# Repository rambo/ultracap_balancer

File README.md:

Series ultracap balancer
========================

Circuits to monitor and balance multiple ultracaps connected to a series.

## 6-Way balancer

[6way.sch](./6way.sch): for 6 Maxel 2600F 2.5V boostcaps in series, balanced
by discharging each cap through 1Ohm resistor as needed.

IMCOMPLETE DESIGN, DO NOT USE.

## FAN7385 & DMG9926 breakout

[fan7385_breakout.sch](./fan7385_breakout.sch): Breaks out both chips to 100mil 
pin headers, the parts can be separated by cutting the board, has the likely connections
either pre-made or available via solder jumpers.

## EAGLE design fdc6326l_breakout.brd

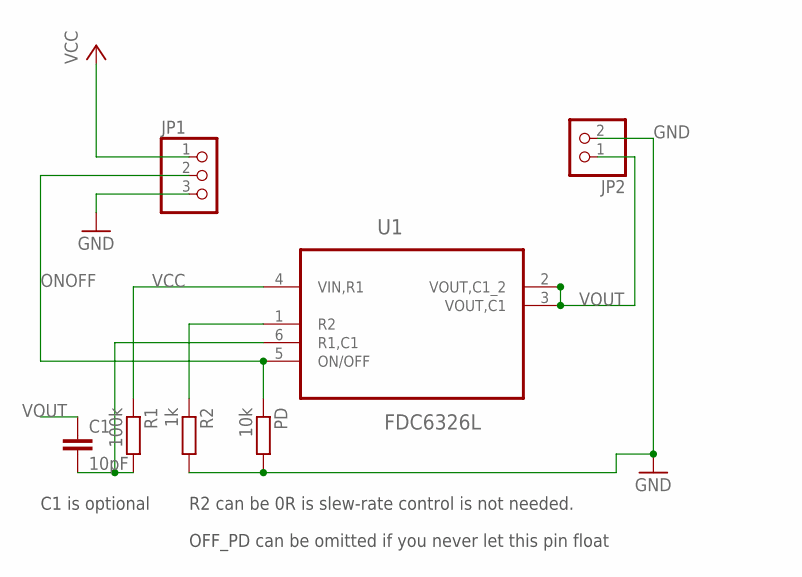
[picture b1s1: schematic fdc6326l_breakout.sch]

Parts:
C1: 10pF; C0603
JP1: PINHD-1X3; 1X03
JP2: PINHD-1X2; 1X02
PD: 10k; R0603
R1: 100k; R0603
R2: 1k; R0603
U1: FDC6326L; SOT95P280X110-6N

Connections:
C1_R1: C1.2, R1.2, U1.6 (R1,C1)
GND: JP1.3, JP2.2, PD.2, R2.2
ONOFF: JP1.2, PD.1, U1.5 (ON/OFF)
R2: R2.1, U1.1 (R2)
VCC: JP1.1, R1.1, U1.4 (VIN,R1)
VOUT: C1.1, JP2.1, U1.2 (VOUT,C1_2), U1.3 (VOUT,C1)

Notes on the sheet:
C1 is optional
R2 can be 0R is slew-rate control is not needed.
OFF_PD can be omitted if you never let this pin float

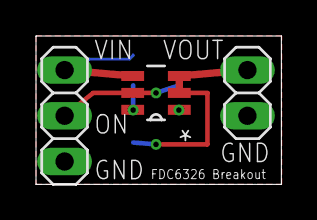
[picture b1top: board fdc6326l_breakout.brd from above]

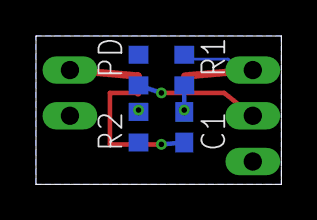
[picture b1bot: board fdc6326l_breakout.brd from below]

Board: 4 copper layers, 13.6 x 8.2 mm, 7 parts (4 on the bottom side), 6 nets.

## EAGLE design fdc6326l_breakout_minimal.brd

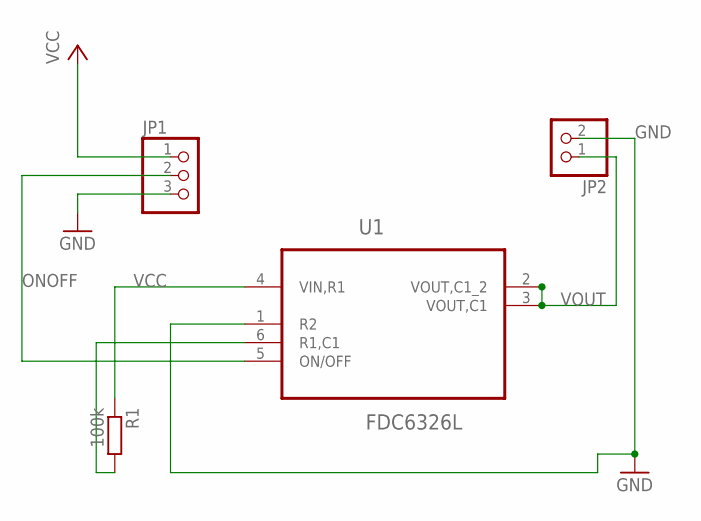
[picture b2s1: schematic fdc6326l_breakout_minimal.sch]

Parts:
JP1: PINHD-1X3; 1X03
JP2: PINHD-1X2; 1X02
R1: 100k; M0805
U1: FDC6326L; SOT95P280X110-6N

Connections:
GND: JP1.3, JP2.2, U1.1 (R2)
unnamed: R1.2, U1.6 (R1,C1)
ONOFF: JP1.2, U1.5 (ON/OFF)
VCC: JP1.1, R1.1, U1.4 (VIN,R1)
VOUT: JP2.1, U1.2 (VOUT,C1_2), U1.3 (VOUT,C1)

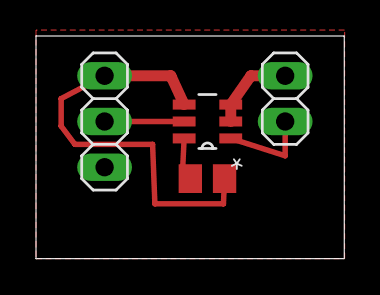
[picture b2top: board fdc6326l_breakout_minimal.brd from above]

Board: 1 copper layer, 17.1 x 12.4 mm, 4 parts (0 on the bottom side), 5 nets.

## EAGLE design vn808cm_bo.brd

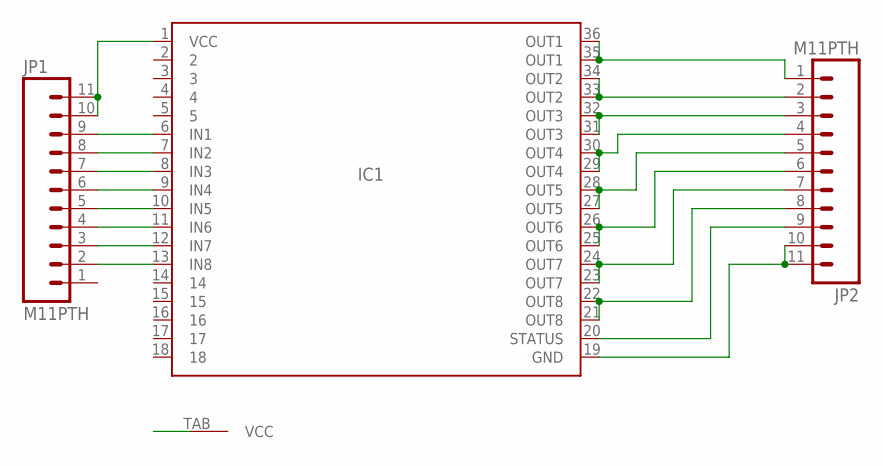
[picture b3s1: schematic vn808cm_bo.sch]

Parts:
IC1: VN808CM-E; POWERSO-36
JP1, JP2: M11PTH; 1X11

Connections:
GND: IC1.19 (GND), JP2.10, JP2.11
IN1: IC1.6 (IN1), JP1.9
IN2: IC1.7 (IN2), JP1.8
IN3: IC1.8 (IN3), JP1.7
IN4: IC1.9 (IN4), JP1.6
IN5: IC1.10 (IN5), JP1.5
IN6: IC1.11 (IN6), JP1.4
IN7: IC1.12 (IN7), JP1.3
IN8: IC1.13 (IN8), JP1.2
OUT1: IC1.35 (OUT1), IC1.36 (OUT1), JP2.1
OUT2: IC1.33 (OUT2), IC1.34 (OUT2), JP2.2
OUT3: IC1.31 (OUT3), IC1.32 (OUT3), JP2.3
OUT4: IC1.29 (OUT4), IC1.30 (OUT4), JP2.4
OUT5: IC1.27 (OUT5), IC1.28 (OUT5), JP2.5
OUT6: IC1.25 (OUT6), IC1.26 (OUT6), JP2.6
OUT7: IC1.23 (OUT7), IC1.24 (OUT7), JP2.7
OUT8: IC1.21 (OUT8), IC1.22 (OUT8), JP2.8
STATUS: IC1.20 (STATUS), JP2.9
VCC: IC1.1 (VCC), IC1.TAB (VCC), JP1.10, JP1.11

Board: 2 copper layers, 3 parts (0 on the bottom side), 19 nets, no tracks yet.

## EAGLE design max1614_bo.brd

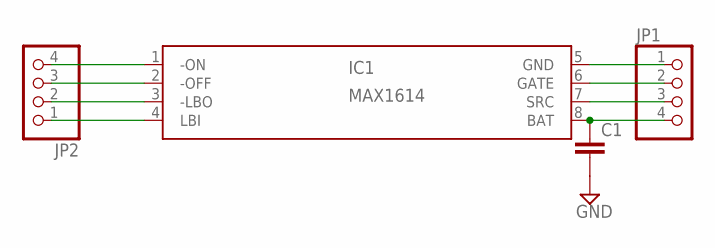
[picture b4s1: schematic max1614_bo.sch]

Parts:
C1: C-EUC0805; C0805
IC1: MAX1614; UMAX8
JP1, JP2: PINHD-1X4; 1X04

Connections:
-LBO: IC1.3 (-LBO), JP2.2
-OFF: IC1.2 (-OFF), JP2.3
-ON: IC1.1 (-ON), JP2.4
BAT: C1.1, IC1.8 (BAT), JP1.4
GATE: IC1.6 (GATE), JP1.2
GND: C1.2, IC1.5 (GND), JP1.1
LBI: IC1.4 (LBI), JP2.1
SRC: IC1.7 (SRC), JP1.3

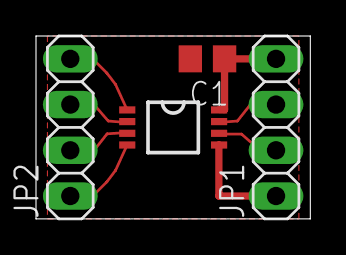
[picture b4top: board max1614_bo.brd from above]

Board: 1 copper layer, 15.2 x 10.2 mm, 4 parts (0 on the bottom side), 8 nets.

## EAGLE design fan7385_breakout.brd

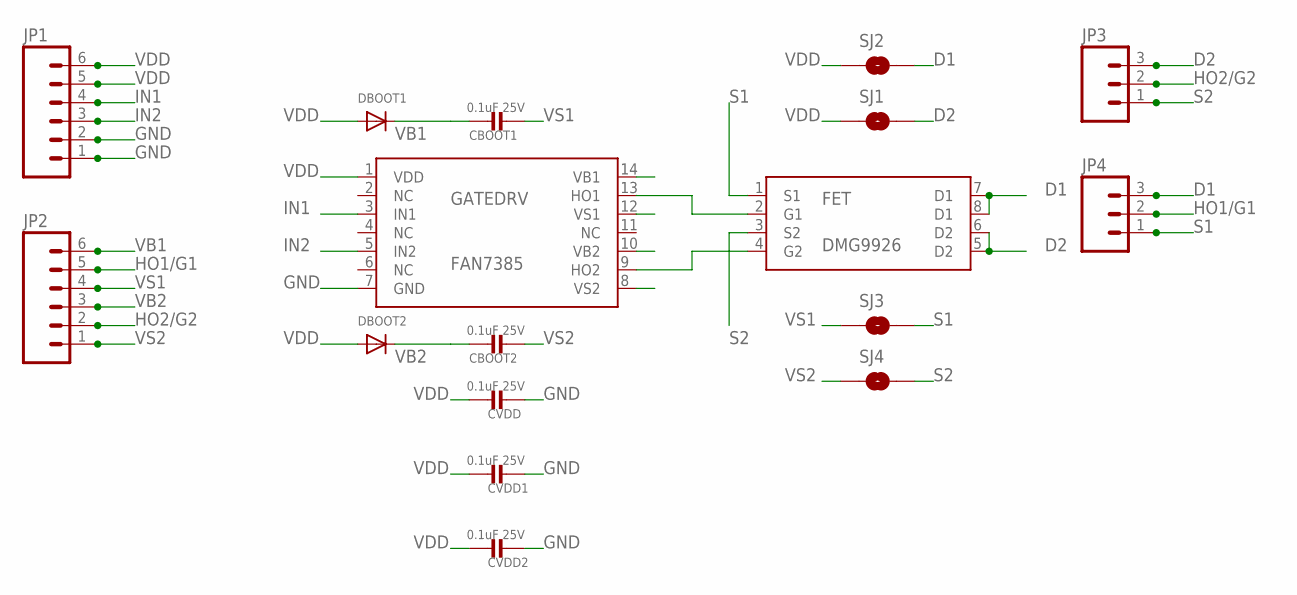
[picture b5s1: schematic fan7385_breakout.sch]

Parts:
CBOOT1, CBOOT2: 0.1uF 25V; 0805
CVDD, CVDD1, CVDD2: 0.1uF 25V; 0805
DBOOT1, DBOOT2: DIODESOT23_WIDE; SOT23-WIDE
FET: DMG9926; SOP8-L
GATEDRV: FAN7385; SOT14
JP1, JP2: M06SIP; 1X06
JP3, JP4: M03PTH; 1X03
SJ1, SJ2: SOLDERJUMPERNO; SJ_2S-NO
SJ3, SJ4: SOLDERJUMPERTRACE; SJ_2S-TRACE

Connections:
D1: FET.7 (D1), FET.8 (D1), JP4.3, SJ2.2
D2: FET.5 (D2), FET.6 (D2), JP3.3, SJ1.2
GND: CVDD.1, CVDD1.1, CVDD2.1, GATEDRV.7 (GND), JP1.1, JP1.2
HO1/G1: FET.2 (G1), GATEDRV.13 (HO1), JP2.5, JP4.2
HO2/G2: FET.4 (G2), GATEDRV.9 (HO2), JP2.2, JP3.2
IN1: GATEDRV.3 (IN1), JP1.4
IN2: GATEDRV.5 (IN2), JP1.3
S1: FET.1 (S1), JP4.1, SJ3.2
S2: FET.3 (S2), JP3.1, SJ4.2
VB1: CBOOT1.2, DBOOT1.3 (C), GATEDRV.14 (VB1), JP2.6
VB2: CBOOT2.2, DBOOT2.3 (C), GATEDRV.10 (VB2), JP2.3
VDD: CVDD.2, CVDD1.2, CVDD2.2, DBOOT1.1 (A), DBOOT2.1 (A), GATEDRV.1 (VDD), JP1.5, JP1.6, SJ1.1, SJ2.1
VS1: CBOOT1.1, GATEDRV.12 (VS1), JP2.4, SJ3.1
VS2: CBOOT2.1, GATEDRV.8 (VS2), JP2.1, SJ4.1

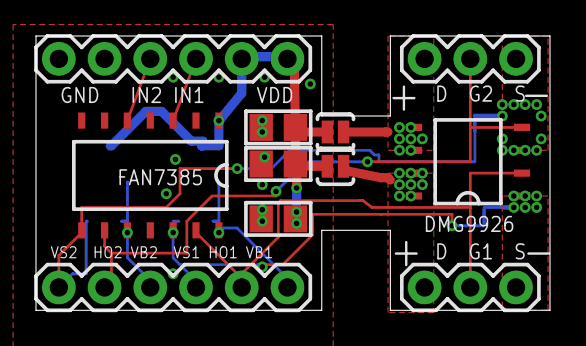
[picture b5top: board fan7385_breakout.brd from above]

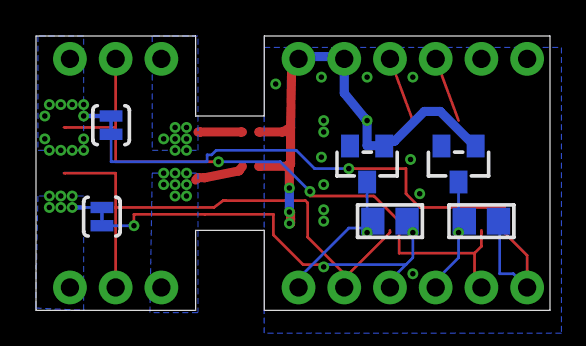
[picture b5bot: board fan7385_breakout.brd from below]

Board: 2 copper layers, 28.6 x 15.2 mm, 17 parts (6 on the bottom side), 14 nets.

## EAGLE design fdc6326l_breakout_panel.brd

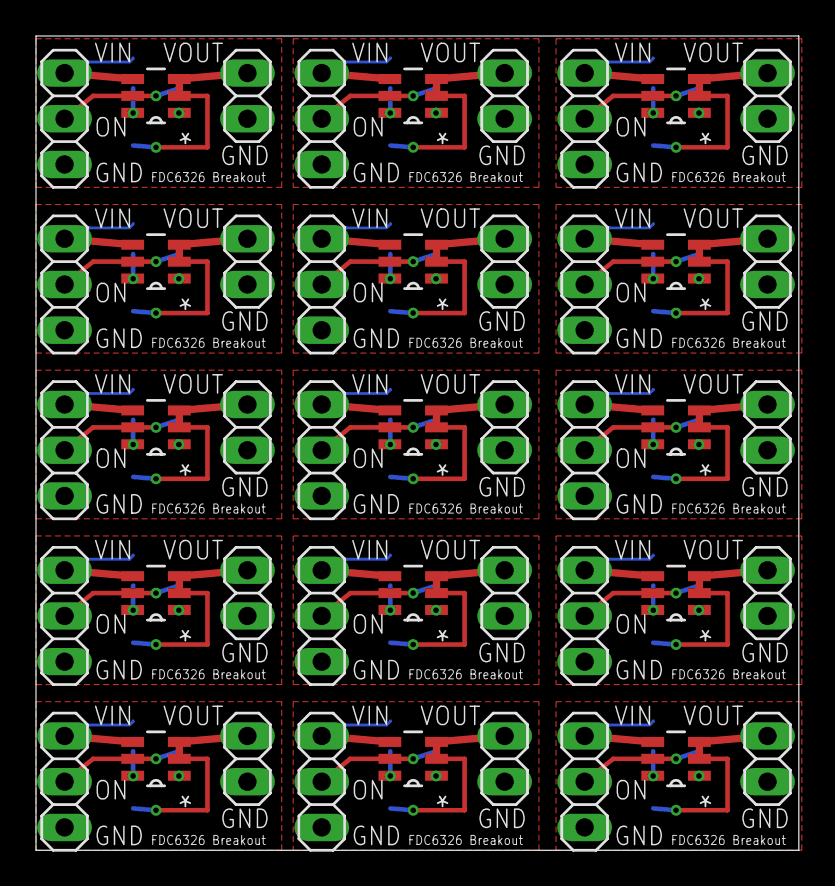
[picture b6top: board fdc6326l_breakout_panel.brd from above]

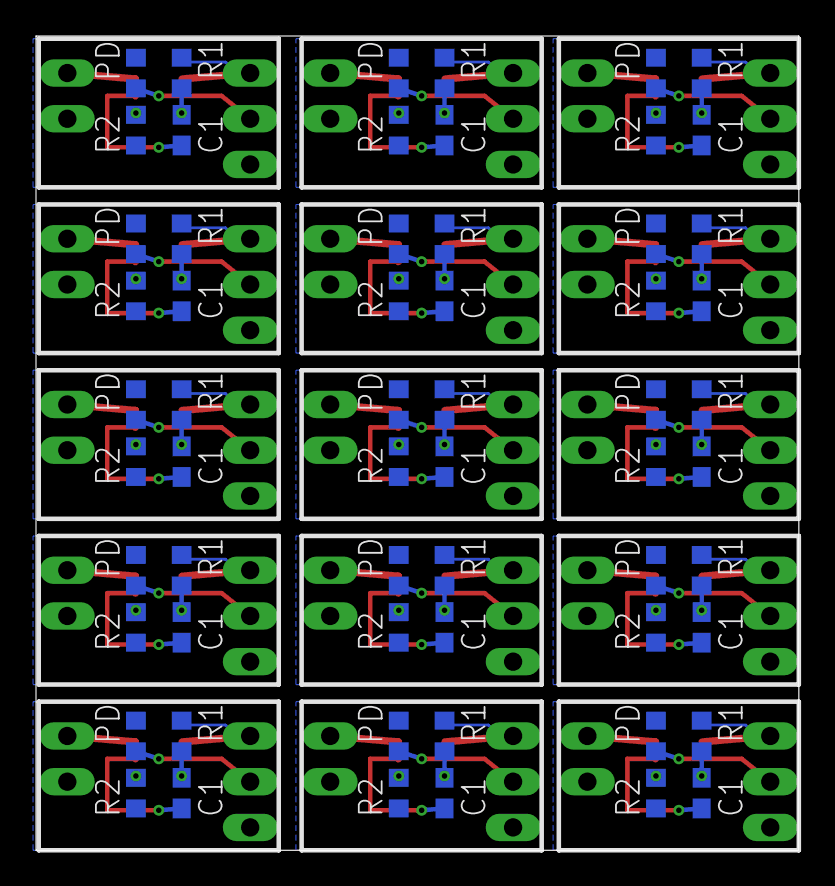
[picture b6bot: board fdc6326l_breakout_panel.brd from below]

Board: 4 copper layers, 42.4 x 45.2 mm, 105 parts (60 on the bottom side), 90 nets.

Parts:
C1, C2, C3, C4, C5, C6, C7, C8, C9, C10, C11, C12, C13, C14, C15: 10pF; C0603
JP1, JP3, JP5, JP7, JP9, JP11, JP13, JP15, JP17, JP19, JP21, JP23, JP25, JP27, JP29: 1X03
JP2, JP4, JP6, JP8, JP10, JP12, JP14, JP16, JP18, JP20, JP22, JP24, JP26, JP28, JP30: 1X02
PD, PD1, PD2, PD3, PD4, PD5, PD6, PD7, PD8, PD9, PD10, PD11, PD12, PD13, PD14: 10k; R0603
R1, R3, R5, R7, R9, R11, R13, R15, R17, R19, R21, R23, R25, R27, R29: 100k; R0603
R2, R4, R6, R8, R10, R12, R14, R16, R18, R20, R22, R24, R26, R28, R30: 1k; R0603
U1, U2, U3, U4, U5, U6, U7, U8, U9, U10, U11, U12, U13, U14, U15: FDC6326L; SOT95P280X110-6N

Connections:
C1_R1: C1.2, R1.2, U1.6
C1_R2: C2.2, R3.2, U2.6
C1_R3: C3.2, R5.2, U3.6
C1_R4: C4.2, R7.2, U4.6
C1_R5: C5.2, R9.2, U5.6
C1_R6: C6.2, R11.2, U6.6
C1_R7: C7.2, R13.2, U7.6
C1_R8: C8.2, R15.2, U8.6
C1_R9: C9.2, R17.2, U9.6
C1_R10: C10.2, R19.2, U10.6
C1_R11: C11.2, R21.2, U11.6
C1_R12: C12.2, R23.2, U12.6
C1_R13: C13.2, R25.2, U13.6
C1_R14: C14.2, R27.2, U14.6
C1_R15: C15.2, R29.2, U15.6
GND: JP1.3, JP2.2, PD.2, R2.2
GND1: JP3.3, JP4.2, PD1.2, R4.2
GND2: JP5.3, JP6.2, PD2.2, R6.2
GND3: JP7.3, JP8.2, PD3.2, R8.2
GND4: JP9.3, JP10.2, PD4.2, R10.2
GND5: JP11.3, JP12.2, PD5.2, R12.2
GND6: JP13.3, JP14.2, PD6.2, R14.2
GND7: JP15.3, JP16.2, PD7.2, R16.2
GND8: JP17.3, JP18.2, PD8.2, R18.2
GND9: JP19.3, JP20.2, PD9.2, R20.2
GND10: JP21.3, JP22.2, PD10.2, R22.2
GND11: JP23.3, JP24.2, PD11.2, R24.2
GND12: JP25.3, JP26.2, PD12.2, R26.2
GND13: JP27.3, JP28.2, PD13.2, R28.2
GND14: JP29.3, JP30.2, PD14.2, R30.2
ONOFF: JP1.2, PD.1, U1.5
ONOFF1: JP3.2, PD1.1, U2.5
ONOFF2: JP5.2, PD2.1, U3.5
ONOFF3: JP7.2, PD3.1, U4.5
ONOFF4: JP9.2, PD4.1, U5.5
ONOFF5: JP11.2, PD5.1, U6.5
ONOFF6: JP13.2, PD6.1, U7.5
ONOFF7: JP15.2, PD7.1, U8.5
ONOFF8: JP17.2, PD8.1, U9.5
ONOFF9: JP19.2, PD9.1, U10.5
ONOFF10: JP21.2, PD10.1, U11.5
ONOFF11: JP23.2, PD11.1, U12.5
ONOFF12: JP25.2, PD12.1, U13.5
ONOFF13: JP27.2, PD13.1, U14.5
ONOFF14: JP29.2, PD14.1, U15.5
R1: R4.1, U2.1
R2: R2.1, U1.1
R3: R6.1, U3.1
R4: R8.1, U4.1
R5: R10.1, U5.1
R6: R12.1, U6.1
R7: R14.1, U7.1
R8: R16.1, U8.1
R9: R18.1, U9.1
R10: R20.1, U10.1
R11: R22.1, U11.1
R12: R24.1, U12.1
R13: R26.1, U13.1
R14: R28.1, U14.1
R15: R30.1, U15.1
VCC: JP1.1, R1.1, U1.4
VCC1: JP3.1, R3.1, U2.4
VCC2: JP5.1, R5.1, U3.4
VCC3: JP7.1, R7.1, U4.4
VCC4: JP9.1, R9.1, U5.4
VCC5: JP11.1, R11.1, U6.4
VCC6: JP13.1, R13.1, U7.4
VCC7: JP15.1, R15.1, U8.4
VCC8: JP17.1, R17.1, U9.4
VCC9: JP19.1, R19.1, U10.4
VCC10: JP21.1, R21.1, U11.4
VCC11: JP23.1, R23.1, U12.4
VCC12: JP25.1, R25.1, U13.4
VCC13: JP27.1, R27.1, U14.4
VCC14: JP29.1, R29.1, U15.4
VOUT: C1.1, JP2.1, U1.2, U1.3
VOUT1: C2.1, JP4.1, U2.2, U2.3
VOUT2: C3.1, JP6.1, U3.2, U3.3
VOUT3: C4.1, JP8.1, U4.2, U4.3
VOUT4: C5.1, JP10.1, U5.2, U5.3
VOUT5: C6.1, JP12.1, U6.2, U6.3
VOUT6: C7.1, JP14.1, U7.2, U7.3
VOUT7: C8.1, JP16.1, U8.2, U8.3
VOUT8: C9.1, JP18.1, U9.2, U9.3
VOUT9: C10.1, JP20.1, U10.2, U10.3
VOUT10: C11.1, JP22.1, U11.2, U11.3
VOUT11: C12.1, JP24.1, U12.2, U12.3
VOUT12: C13.1, JP26.1, U13.2, U13.3
VOUT13: C14.1, JP28.1, U14.2, U14.3
VOUT14: C15.1, JP30.1, U15.2, U15.3

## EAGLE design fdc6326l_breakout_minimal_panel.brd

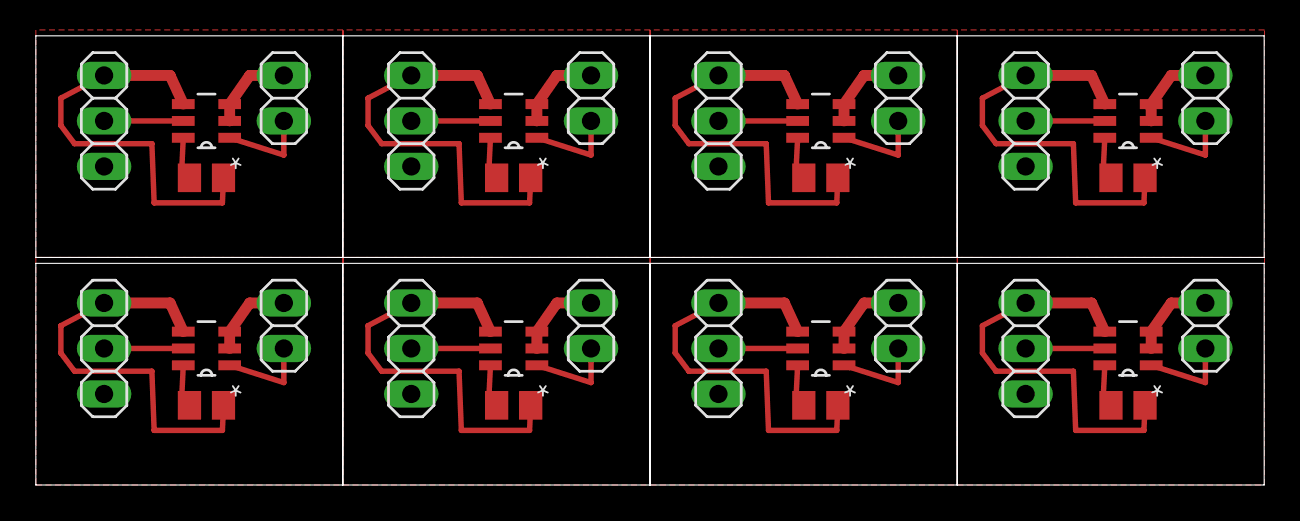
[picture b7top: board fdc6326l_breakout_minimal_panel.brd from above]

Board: 1 copper layer, 68.6 x 25.1 mm, 32 parts (0 on the bottom side), 40 nets.

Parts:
JP1, JP3, JP5, JP7, JP9, JP11, JP13, JP15: 1X03
JP2, JP4, JP6, JP8, JP10, JP12, JP14, JP16: 1X02
R1, R2, R3, R4, R5, R6, R7, R8: 100k; M0805
U1, U2, U3, U4, U5, U6, U7, U8: FDC6326L; SOT95P280X110-6N

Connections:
GND: JP1.3, JP2.2, U1.1
GND1: JP3.3, JP4.2, U2.1
GND2: JP5.3, JP6.2, U3.1
GND3: JP7.3, JP8.2, U4.1
GND4: JP9.3, JP10.2, U5.1
GND5: JP11.3, JP12.2, U6.1
GND6: JP13.3, JP14.2, U7.1
GND7: JP15.3, JP16.2, U8.1
unnamed: R2.2, U2.6
unnamed: R3.2, U3.6
unnamed: R1.2, U1.6
unnamed: R4.2, U4.6
unnamed: R5.2, U5.6
unnamed: R6.2, U6.6
unnamed: R7.2, U7.6
unnamed: R8.2, U8.6
ONOFF: JP1.2, U1.5
ONOFF1: JP3.2, U2.5
ONOFF2: JP5.2, U3.5
ONOFF3: JP7.2, U4.5
ONOFF4: JP9.2, U5.5
ONOFF5: JP11.2, U6.5
ONOFF6: JP13.2, U7.5
ONOFF7: JP15.2, U8.5
VCC: JP1.1, R1.1, U1.4
VCC1: JP3.1, R2.1, U2.4
VCC2: JP5.1, R3.1, U3.4
VCC3: JP7.1, R4.1, U4.4
VCC4: JP9.1, R5.1, U5.4
VCC5: JP11.1, R6.1, U6.4
VCC6: JP13.1, R7.1, U7.4
VCC7: JP15.1, R8.1, U8.4
VOUT: JP2.1, U1.2, U1.3
VOUT1: JP4.1, U2.2, U2.3
VOUT2: JP6.1, U3.2, U3.3
VOUT3: JP8.1, U4.2, U4.3
VOUT4: JP10.1, U5.2, U5.3
VOUT5: JP12.1, U6.2, U6.3
VOUT6: JP14.1, U7.2, U7.3
VOUT7: JP16.1, U8.2, U8.3

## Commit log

2013-03-23 started working
2013-03-23 sense opamps for a single pair of caps
2013-03-23 sot14 package definition
2013-03-23 maybe it is now correctly connected
2013-03-23 added the gatedriver from the lib
2013-03-23 library for the dual-mosfet
2013-03-23 and added the dual-mosfet to the schematic¨
2013-03-23 make the NC pins use the @trick with their names
2013-03-23 wired the signals that I know to handle, next up is figuring out the rest of it, datasheet is a bit sparse on details here
2013-03-23 this I still knew how to do
2013-03-23 started to make the bootsrap circuit for the gate driver
2013-03-23 Bus for the sense/control signals
2013-03-23 use solder jumper with trace to separate small-signal nets from the high-current ones
2013-03-23 fix the net classes for the new small-signal versions
2013-03-23 made two more groups of 2, and what fun will I have renaming all the nets...
2013-03-23 removed the other group for now and renamed all the nets in the first copy
2013-03-23 third groups renames and a missed small-signal rename
2013-03-23 make these only power nets, I will do a separate high-power 12V net if I am going to need it
2013-03-23 minor update
2013-03-25 making a breakout to test the driver and mosfet
2013-03-25 added the pin-headers
2013-03-25 initial layout
2013-03-25 GND polygons for the gate driver
2013-03-25 loaded Seeed DRU
2013-03-25 autorouted
2013-03-25 polygons on the mosfer high-current signals
2013-03-25 make the signal back from drains to the driver normal instead of high-power
2013-03-25 one more signal rename
2013-03-25 minor layout adjustments
2013-03-25 I guess the huge grid would explain why routing failed...
2013-03-25 a bit of manual routing, hoping it will help
2013-03-25 switched to octagon pads to solve a clearance issue
2013-03-25 route some more stuff manually first, adjust shape for symmetry
2013-03-25 diffeent pin header part and 100mil spacing between pins
2013-03-25 moved parts around a bit, put the bypass cap to gnd using vias
2013-03-25 labels and optimizing size
2013-03-25 adjusted mosfet position to allow for pin labels
2013-03-25 actually if these are to be used together the pin aligment must match...
2013-03-25 fixed clearance issue
2013-03-25 ERC details
2013-03-25 one more label
2013-03-25 ignore eagle tmp files and add image of the breakout board layout
2013-03-25 added some caps
2013-03-25 route some bits manually
2013-03-25 removed a cap to help with routing
2013-03-25 two cap routing
2013-03-25 routed
2013-03-25 one more change
2013-05-24 UAAH! mixed source and drain for the cboot return...
2013-05-24 added note needing to fix those reversed connections
2013-05-24 reminder on which direction the current flows....
2013-05-26 these should be connected to drain as well, but now we have a problem with routing
2013-05-26 line up the pin headers to 100mil grid
2013-05-26 finding a way out for the gate signals
2013-05-26 rerouted
2013-09-06 scripted part librayr
2013-09-06 trivial breakout
2013-09-06 ready to route
2013-09-06 use thicker wire here too
2013-09-07 move the dimension a bit, now if you make the mistake of printing it out for etching it will short the pins...
2013-10-23 trying to make a part of this funky package
2013-10-23 the bdsl I used to autogenerated the basis for the library
2013-10-23 it seems a polygon cannot have a name
2013-10-23 labels, connections
2013-10-23 simple breakout schematic
2013-10-23 placed the components, though in second thought I do not need to pins for GND since that is just for logic
2015-04-21 QnD schematic
2015-04-21 minimal version with no slew or inrush control
2015-04-21 simple breakout
2015-04-21 use the part number
2015-04-22 move the polygon to the board edge
2015-04-22 panelized version
2015-04-22 added pull-down for on/off pin and some notes
2015-04-23 switch to 0603 passives
2015-04-23 b4 autoroute
2015-04-23 make the board smaller
2015-04-23 some texts
2015-04-23 fix polygon
2015-04-23 replace names with vector text
2015-04-23 tigh panel, could (and should) be made less tigh for easier cutting
2015-04-23 less tigh spacing

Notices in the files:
parts and their libraries:
microbuilder: This work is placed in the public domain, and may be freely used for commercial and non-commercial work with the following conditions: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
SparkFun-Passives: Licensing: CC v3.0 Share-Alike You are welcome to use this library for commercial purposes.
